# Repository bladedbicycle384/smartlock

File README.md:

# smartlock
A graduation project for ELSYS school in Bulgaria.

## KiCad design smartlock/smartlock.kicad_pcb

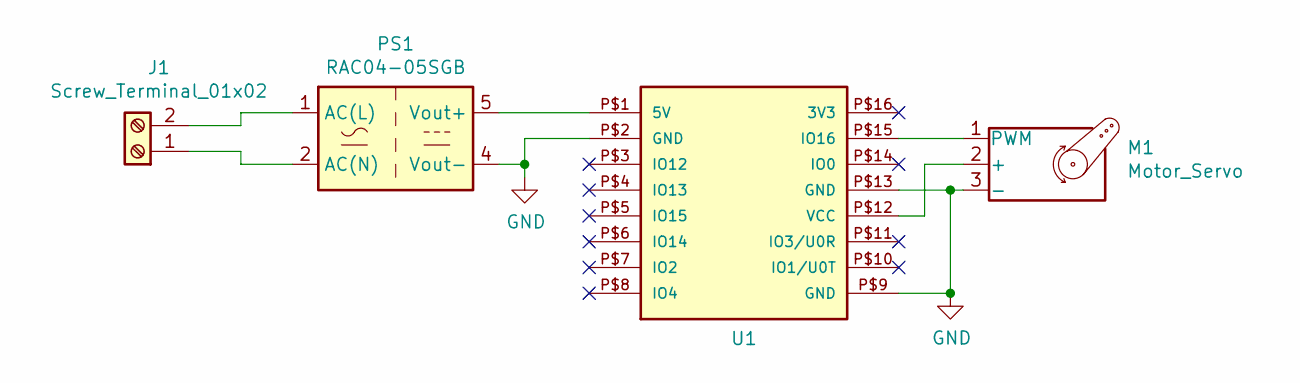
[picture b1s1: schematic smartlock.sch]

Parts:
J1: Screw_Terminal_01x02; TerminalBlock_Phoenix_MKDS-1,5-2_1x02_P5.00mm_Horizontal
M1: Motor_Servo; PinHeader_1x03_P1.00mm_Vertical
PS1: RAC04-05SGB; Converter_ACDC_RECOM_RAC04-xxSGx_THT
U1: ESP32-CAM

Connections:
GND: M1.3 (-), PS1.4 (Vout-), U1.P$2 (GND), U1.P$9 (GND), U1.P$13 (GND)
unnamed: J1.1, PS1.2 (AC(N))
unnamed: J1.2, PS1.1 (AC(L))
unnamed: M1.1 (PWM), U1.P$15 (IO16)
unnamed: M1.2 (+), U1.P$12 (VCC)
unnamed: PS1.5 (Vout+), U1.P$1 (5V)

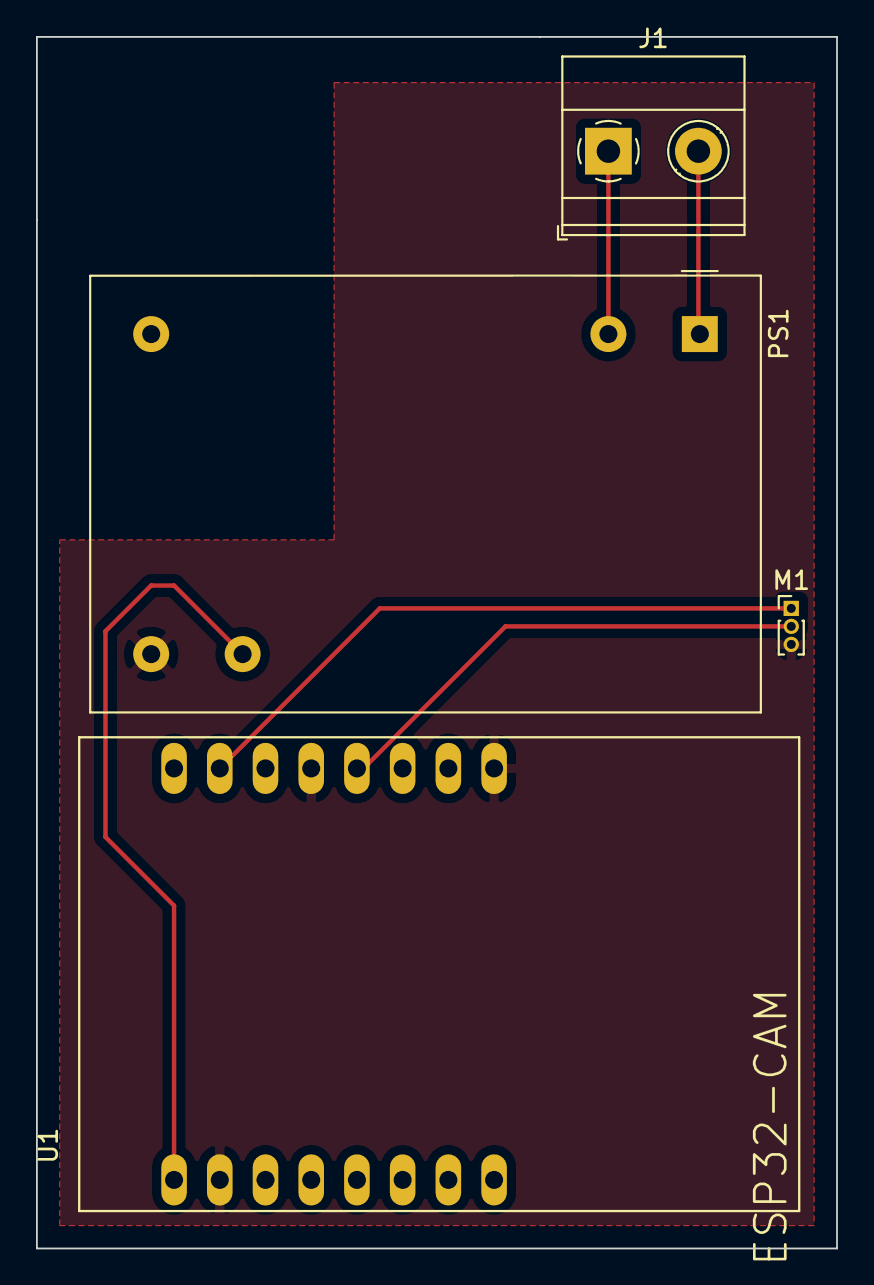
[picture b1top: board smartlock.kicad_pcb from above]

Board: 2 copper layers, 44.5 x 67.3 mm, 4 parts (0 on the bottom side), 6 nets.

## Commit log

2022-03-19 Uploading almost finished code
    I haven't uploaded the project before so this is my first actual commit, I have done most of the basic functionalities, there are some errors coming from using JSON but I am planning on fixing that i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
2022-03-19 Adding the default PlatformIO test README
    Accidentally unmarked the README, adding it as well.
2022-03-29 An old fix that I didn't push
    Reworked and fixed the access list system, now it works. Properly made the code for locking and unlocking the device. Managed to figure out the "deletion" without making it too overkill though I susp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
2022-03-31 Updated the BT connectivity a bit
2022-03-31 fixed up bt a bit again
2022-03-31 Fixed access list extention
2022-04-01 reworked some commands
    went a bit too overboard with tuning it to the point whereit's practically a different code
2022-04-01 Added circuit and documentation
    Documentation is awaiting approval.
2022-04-03 Finalized version
    Left some of the testing methods, serial prints and file creation as comments to demonstrate how it was done, will remove in a later commit.
2022-04-03 Fixed a minor error
2022-04-03 fixed the file setup
2022-04-04 cleaned up the file operations a bit
2022-04-04 Cleaned up
    Cleaned up code from any and all test Serial Prints, used in the video demonstration. The code is longer than the code uploaded on 31.03.2022 due to restructuring and fixing a few errors and mistakes.
2022-04-04 Edited file system and added edit
    Changed up how I work with files a bit, optimized the delete function, added an edit function and fixed up a minor bug with stopping bluetooth connection.
2022-04-09 Final code
    Final version of the code, might include some debugging at a later point but works for now :D
2022-04-10 Cleanup
    Cleaned up the file_setup function to not be too long
2022-04-10 cleaned up
    Yet another cleaning up patch
2022-05-21 Defense ready
    Decided to rework a bit of the code so that it works a tad bit more consistently. Wasn't done in the last second, just remembered to update it now. Also added a function to list all the available key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
